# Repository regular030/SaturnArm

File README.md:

<p align="center">
  
  # SaturnArm - A Simple Robotic Arm
</p>

<p align="center">

  [Youtube Video](https://youtu.be/AQZ1tVmb0GA)
  
  <ul>
<p align="center">
  <br>
  BOM: https://docs.google.com/spreadsheets/d/1lf9XG99qlgez3aRTxvFln9WQ-VlTF8MQk1fM6mLnBtQ/edit?usp=sharing

</p>
    
<h2> Why did I Build This?</h2>
<p>
  While watching a NASA Mars rover in action on YouTube, I noticed how every function, including the robotic arm, was controlled through a computer interface. It made me wonder, why not use virtual reality instead, to make the experience more immersive and intuitive?
</p>

# Files 
- Chassis
  - SaturnArm.gcode.3mf
      - G-code to print out the entire arm for the Bambu Lab A1m
  - arm_pcb.step
    - The PCB's 3D model file
  - Full-Arm.f3z
    - Full Fusion/Fusion 360 file for the arm
  - bot
    - All 3D files for the bottom part of the arm    
  - middle
    - All 3D files for the middle part of the arm    
  - top
    - All 3D files for the top part of the arm
- Kicad
  - All PCB files for KiCad 8.0.5
- Firmware
  - All the Firmware files for the Pi Zero 2 W
- Unity
  -  All the Files for the VR to Arm stuff in Unity 2022.3.38f1
  -  DEPRECATED
      
<ul> </ul>
 
#  Instructions

## Building the Firmware on Raspberry Pi Zero 2 W

**1. Install Required Packages**

Open a terminal on your Pi Zero 2 W and run:
```sh
sudo apt update
sudo apt install -y git cmake g++ libopencv-dev libboost-system-dev pigpio
```

**2. Clone the Repository**
```sh
git clone https://github.com/regular030/SaturnArm
cd SaturnArm/Firmware/Arm
```

**3. Enable pigpio Daemon**
```sh
sudo systemctl enable pigpiod
sudo systemctl start pigpiod
```

**4. Build the Firmware**
```sh
mkdir build
cd build
cmake ..
make -j1
```
The executable `SaturnArm` will be created in the `build` directory.

---

## Calibration

Before using the arm, you must calibrate it:

1. **Remove the Motors:**  
   Remove the motors from the arm.

2. **Run the Firmware:**  
   Start the firmware executable under the build directory:
   ```sh
   sudo ./SaturnArm
   ```

3. **Wait for Program to Run:**  
   Wait for the Program to run, after that wait for the motors to move to 0deg. Once the motors are done moving, make sure the arms are in an upright position before attaching the motors.

---

## Main Functions

- **move_to(x, z):**  
  Move the arm to a specific (x, z) coordinate using inverse kinematics.
     ```sh
   move:(x),(y)
   ```

- **set_servo_angle(servo_number, angle):**  
  Set a specific servo (shoulder, elbow, or claw) to a given angle.
     ```sh
   servo(number):(deg)
   ```

- **emergency_stop():**  
  Immediately stop all motion and disable servos.
  ```sh
   stop
   ```
---

For more details, see the source code in `Firmware/Arm/`.

<ul> </ul>

#  TODO

- Finalize VR Support - Delayed Indefinitely

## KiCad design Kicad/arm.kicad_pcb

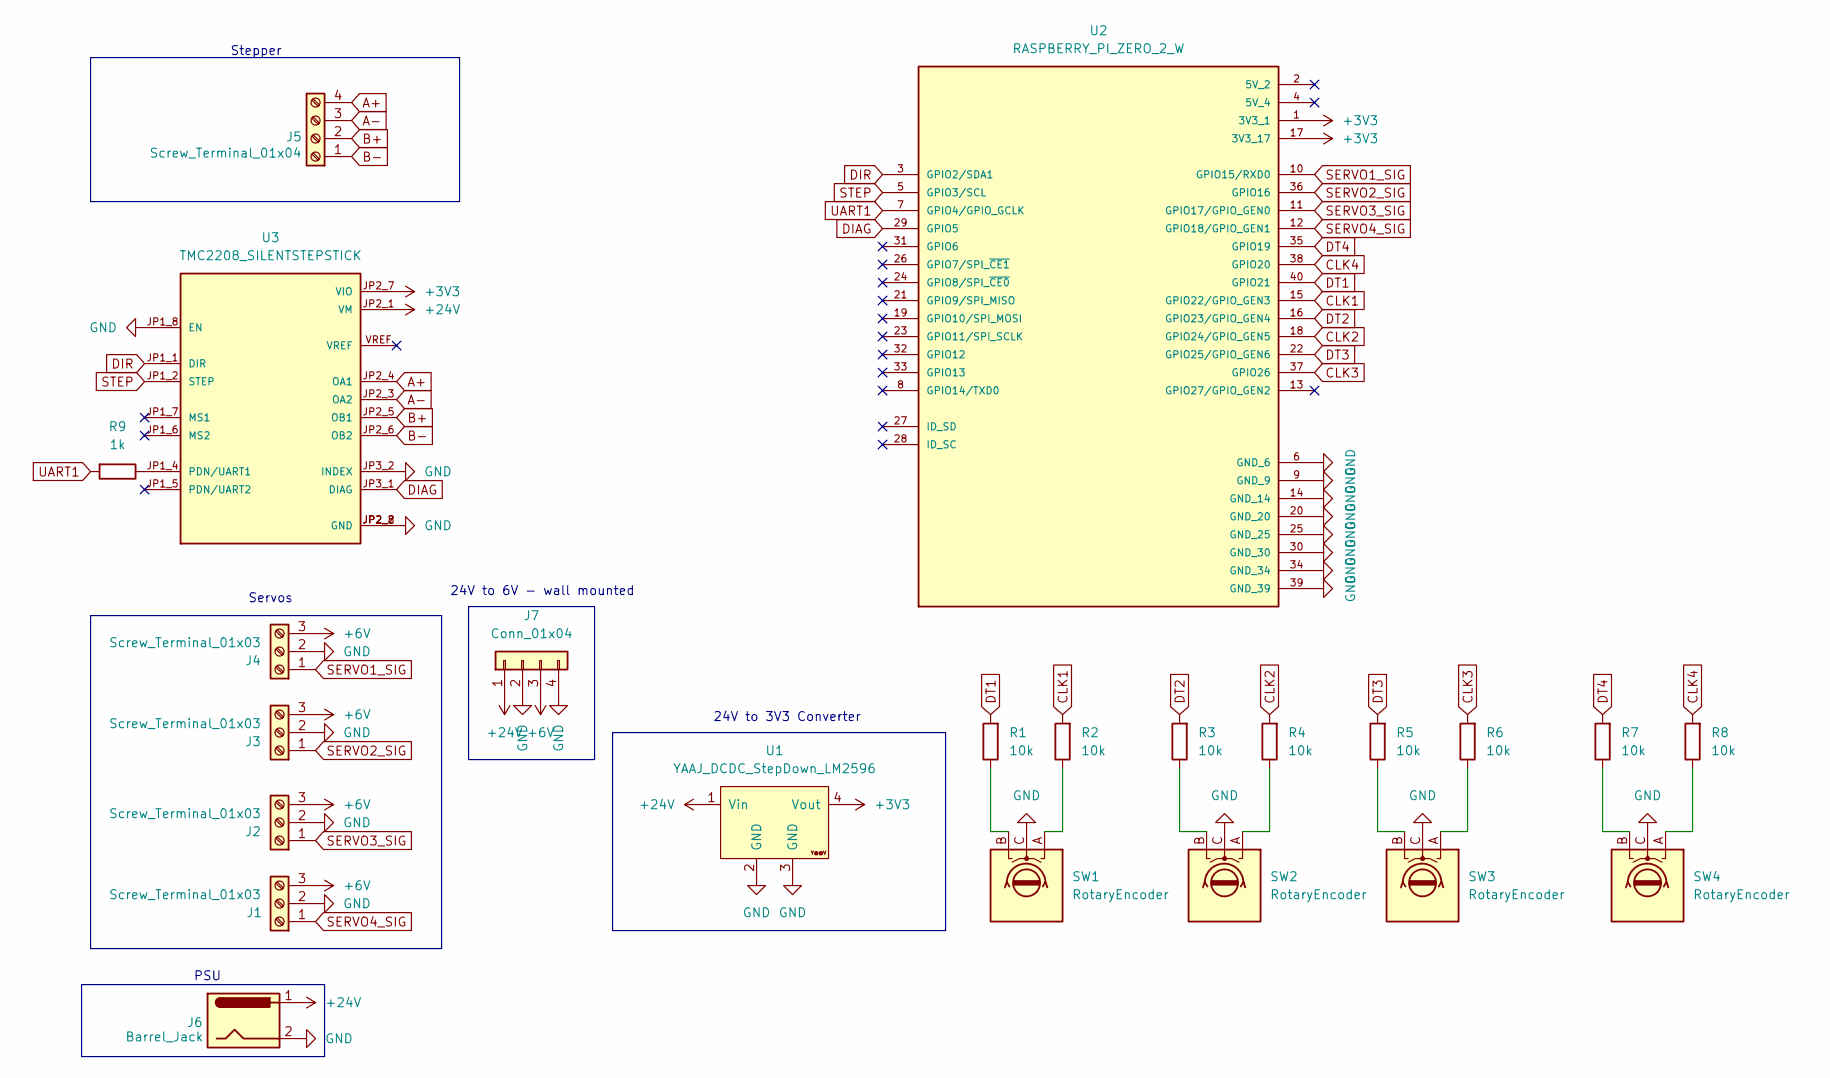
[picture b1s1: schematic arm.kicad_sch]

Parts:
J1, J2, J3, J4: Screw_Terminal_01x03; TerminalBlock_bornier-3_P5.08mm
J5: Screw_Terminal_01x04; TerminalBlock_bornier-4_P5.08mm
J6: Barrel_Jack; BarrelJack_Horizontal
J7: Conn_01x04; PinHeader_1x04_P2.54mm_Vertical
R1, R2, R3, R4, R5, R6, R7, R8: 10k; R_Axial_DIN0207_L6.3mm_D2.5mm_P7.62mm_Horizontal
R9: 1k; R_Axial_DIN0207_L6.3mm_D2.5mm_P7.62mm_Horizontal
SW1, SW2, SW3, SW4: RotaryEncoder; RotaryEncoder_Alps_EC11E-Switch_Vertical_H20mm
U1: YAAJ_DCDC_StepDown_LM2596
U2: RASPBERRY_PI_ZERO_2_W; MODULE_RASPBERRY_PI_ZERO_2_W; PARTREV April 2024
U3: TMC2208_SILENTSTEPSTICK; MODULE_TMC2208_SILENTSTEPSTICK

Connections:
+3V3: U1.4 (Vout), U2.1 (3V3_1), U2.17 (3V3_17), U3.JP2_7 (VIO)
+6V: J1.3, J2.3, J3.3, J4.3, J7.3
+24V: J6.1, J7.1, U1.1 (Vin), U3.JP2_1 (VM)
A+: J5.4, U3.JP2_4 (OA1)
A-: J5.3, U3.JP2_3 (OA2)
B+: J5.2, U3.JP2_5 (OB1)
B-: J5.1, U3.JP2_6 (OB2)
CLK1: R2.2, U2.15 (GPIO22/GPIO_GEN3)
CLK2: R4.2, U2.18 (GPIO24/GPIO_GEN5)
CLK3: R6.2, U2.37 (GPIO26)
CLK4: R8.2, U2.38 (GPIO20)
DIAG: U2.29 (GPIO5), U3.JP3_1 (DIAG)
DIR: U2.3 (GPIO2/SDA1), U3.JP1_1 (DIR)
DT1: R1.2, U2.40 (GPIO21)
DT2: R3.2, U2.16 (GPIO23/GPIO_GEN4)
DT3: R5.2, U2.22 (GPIO25/GPIO_GEN6)
DT4: R7.2, U2.35 (GPIO19)
GND: J1.2, J2.2, J3.2, J4.2, J6.2, J7.2, J7.4, SW1.C, SW2.C, SW3.C, SW4.C, U1.2 (GND), U1.3 (GND), U2.6 (GND_6), U2.9 (GND_9), U2.14 (GND_14), U2.20 (GND_20), U2.25 (GND_25), U2.30 (GND_30), U2.34 (GND_34), U2.39 (GND_39), U3.JP1_8 (EN), U3.JP2_2 (GND), U3.JP2_8 (GND), U3.JP3_2 (INDEX)
unnamed: R1.1, SW1.B
unnamed: R2.1, SW1.A
unnamed: R3.1, SW2.B
unnamed: R4.1, SW2.A
unnamed: R5.1, SW3.B
unnamed: R6.1, SW3.A
unnamed: R7.1, SW4.B
unnamed: R8.1, SW4.A
unnamed: R9.1, U3.JP1_4 (PDN/UART1)
SERVO1_SIG: J4.1, U2.10 (GPIO15/RXD0)
SERVO2_SIG: J3.1, U2.36 (GPIO16)
SERVO3_SIG: J2.1, U2.11 (GPIO17/GPIO_GEN0)
SERVO4_SIG: J1.1, U2.12 (GPIO18/GPIO_GEN1)
STEP: U2.5 (GPIO3/SCL), U3.JP1_2 (STEP)
UART1: R9.2, U2.7 (GPIO4/GPIO_GCLK)

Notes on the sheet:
Servos
Stepper
24V to 6V - wall mounted
24V to 3V3 Converter
PSU

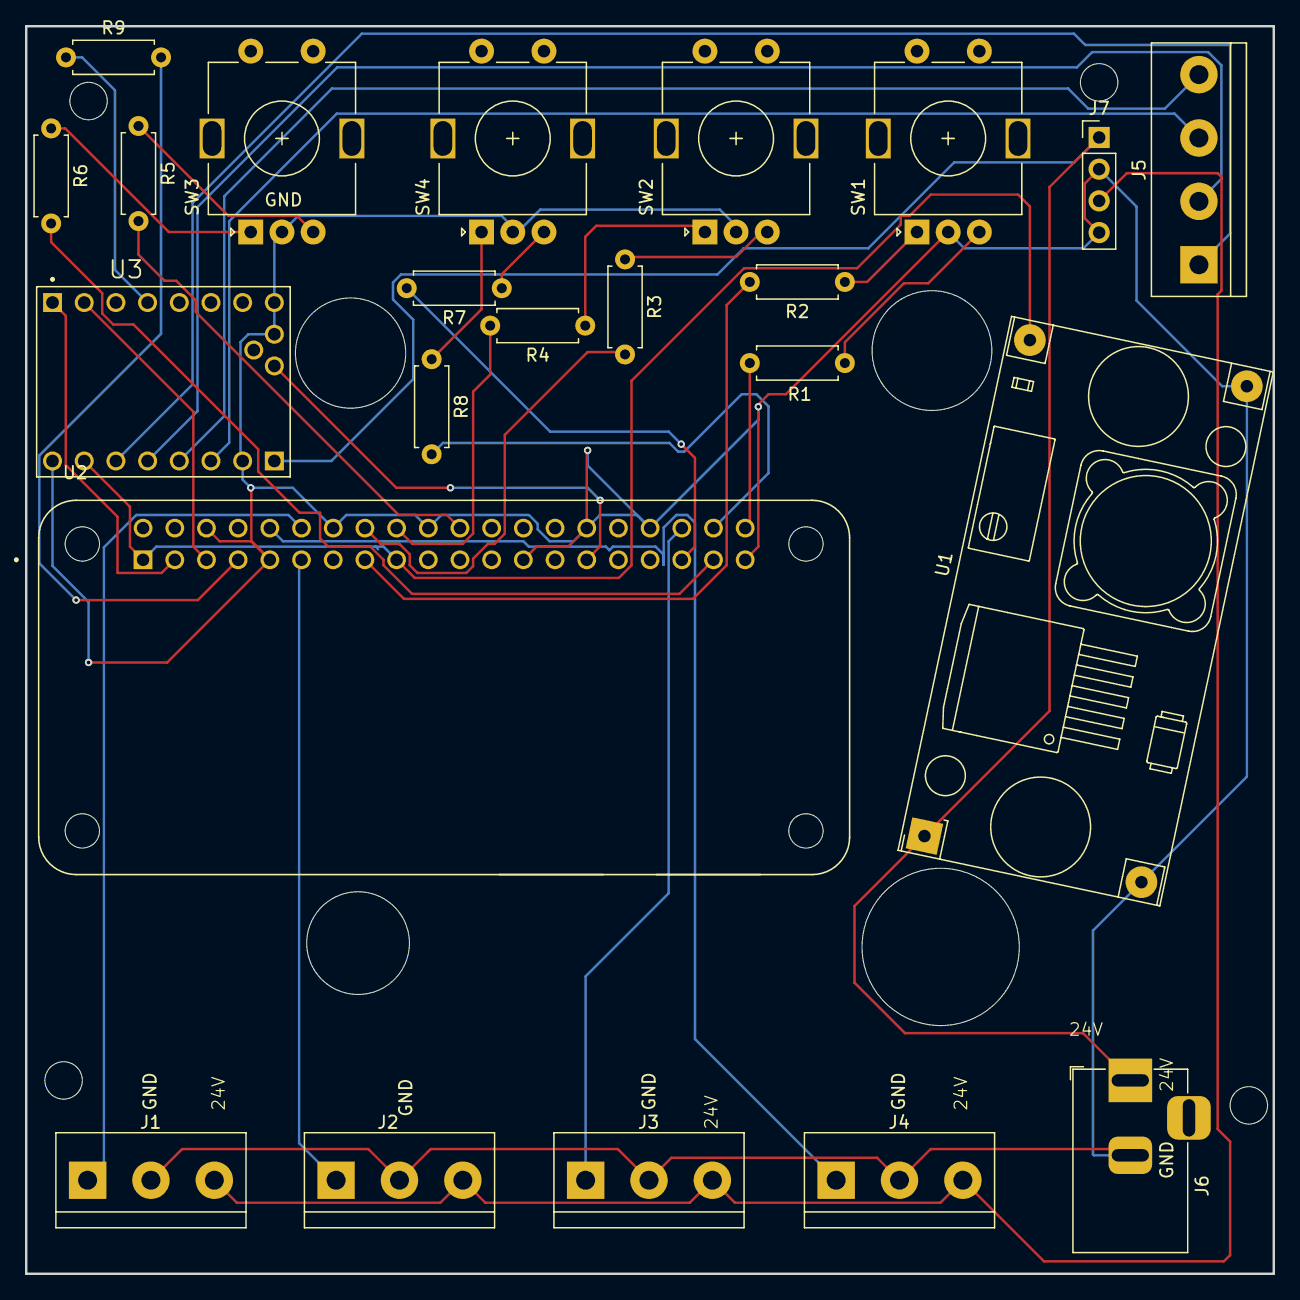
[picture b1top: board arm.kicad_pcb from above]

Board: 2 copper layers, 100.0 x 100.0 mm, 23 parts (0 on the bottom side), 33 nets.

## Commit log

2025-06-03 added gerber files
2025-06-04 Added Full-Arm.f3z
2025-06-04 added the basic arm control
2025-06-07 added hand tracking + controller support
2025-06-07 added controller hand anims
2025-06-08 changed firmware to use pi sdk
2025-06-08 added server functionality to the pi zero 2 w to communicate with unity, Unity code TBF
2025-06-08 updated some stuff
2025-06-10 added code for arm--> unity (although very theortical it mostly works still need to test on physical)
2025-06-10 unity wants to upload these 🥀
2025-06-18 updated stepper insert
2025-06-21 updated gears so instead of replacing the actual gear, i just mount it, updated stls/steps + 3mf file
2025-06-24 updated 3D files + removed old code and currently migrating it from pi pico -> pi zero
2025-06-24 few updates to code
2025-06-24 updated files
2025-06-24 removed wifi login (not used)
2025-06-24 update code
2025-08-03 update files
2025-08-04 added servo test
2025-08-06 added min and max def
2025-08-07 updated kinematics
